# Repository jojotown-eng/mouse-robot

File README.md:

# mouse-robot
マイクロマウスで使用するデータを入れておくリポジトリ

### design
機体のcadデータを入れるファイル

### firmware
マウス内のプログラムデータを入れるフォルダ

### PCB
基板関連のデータを入れる

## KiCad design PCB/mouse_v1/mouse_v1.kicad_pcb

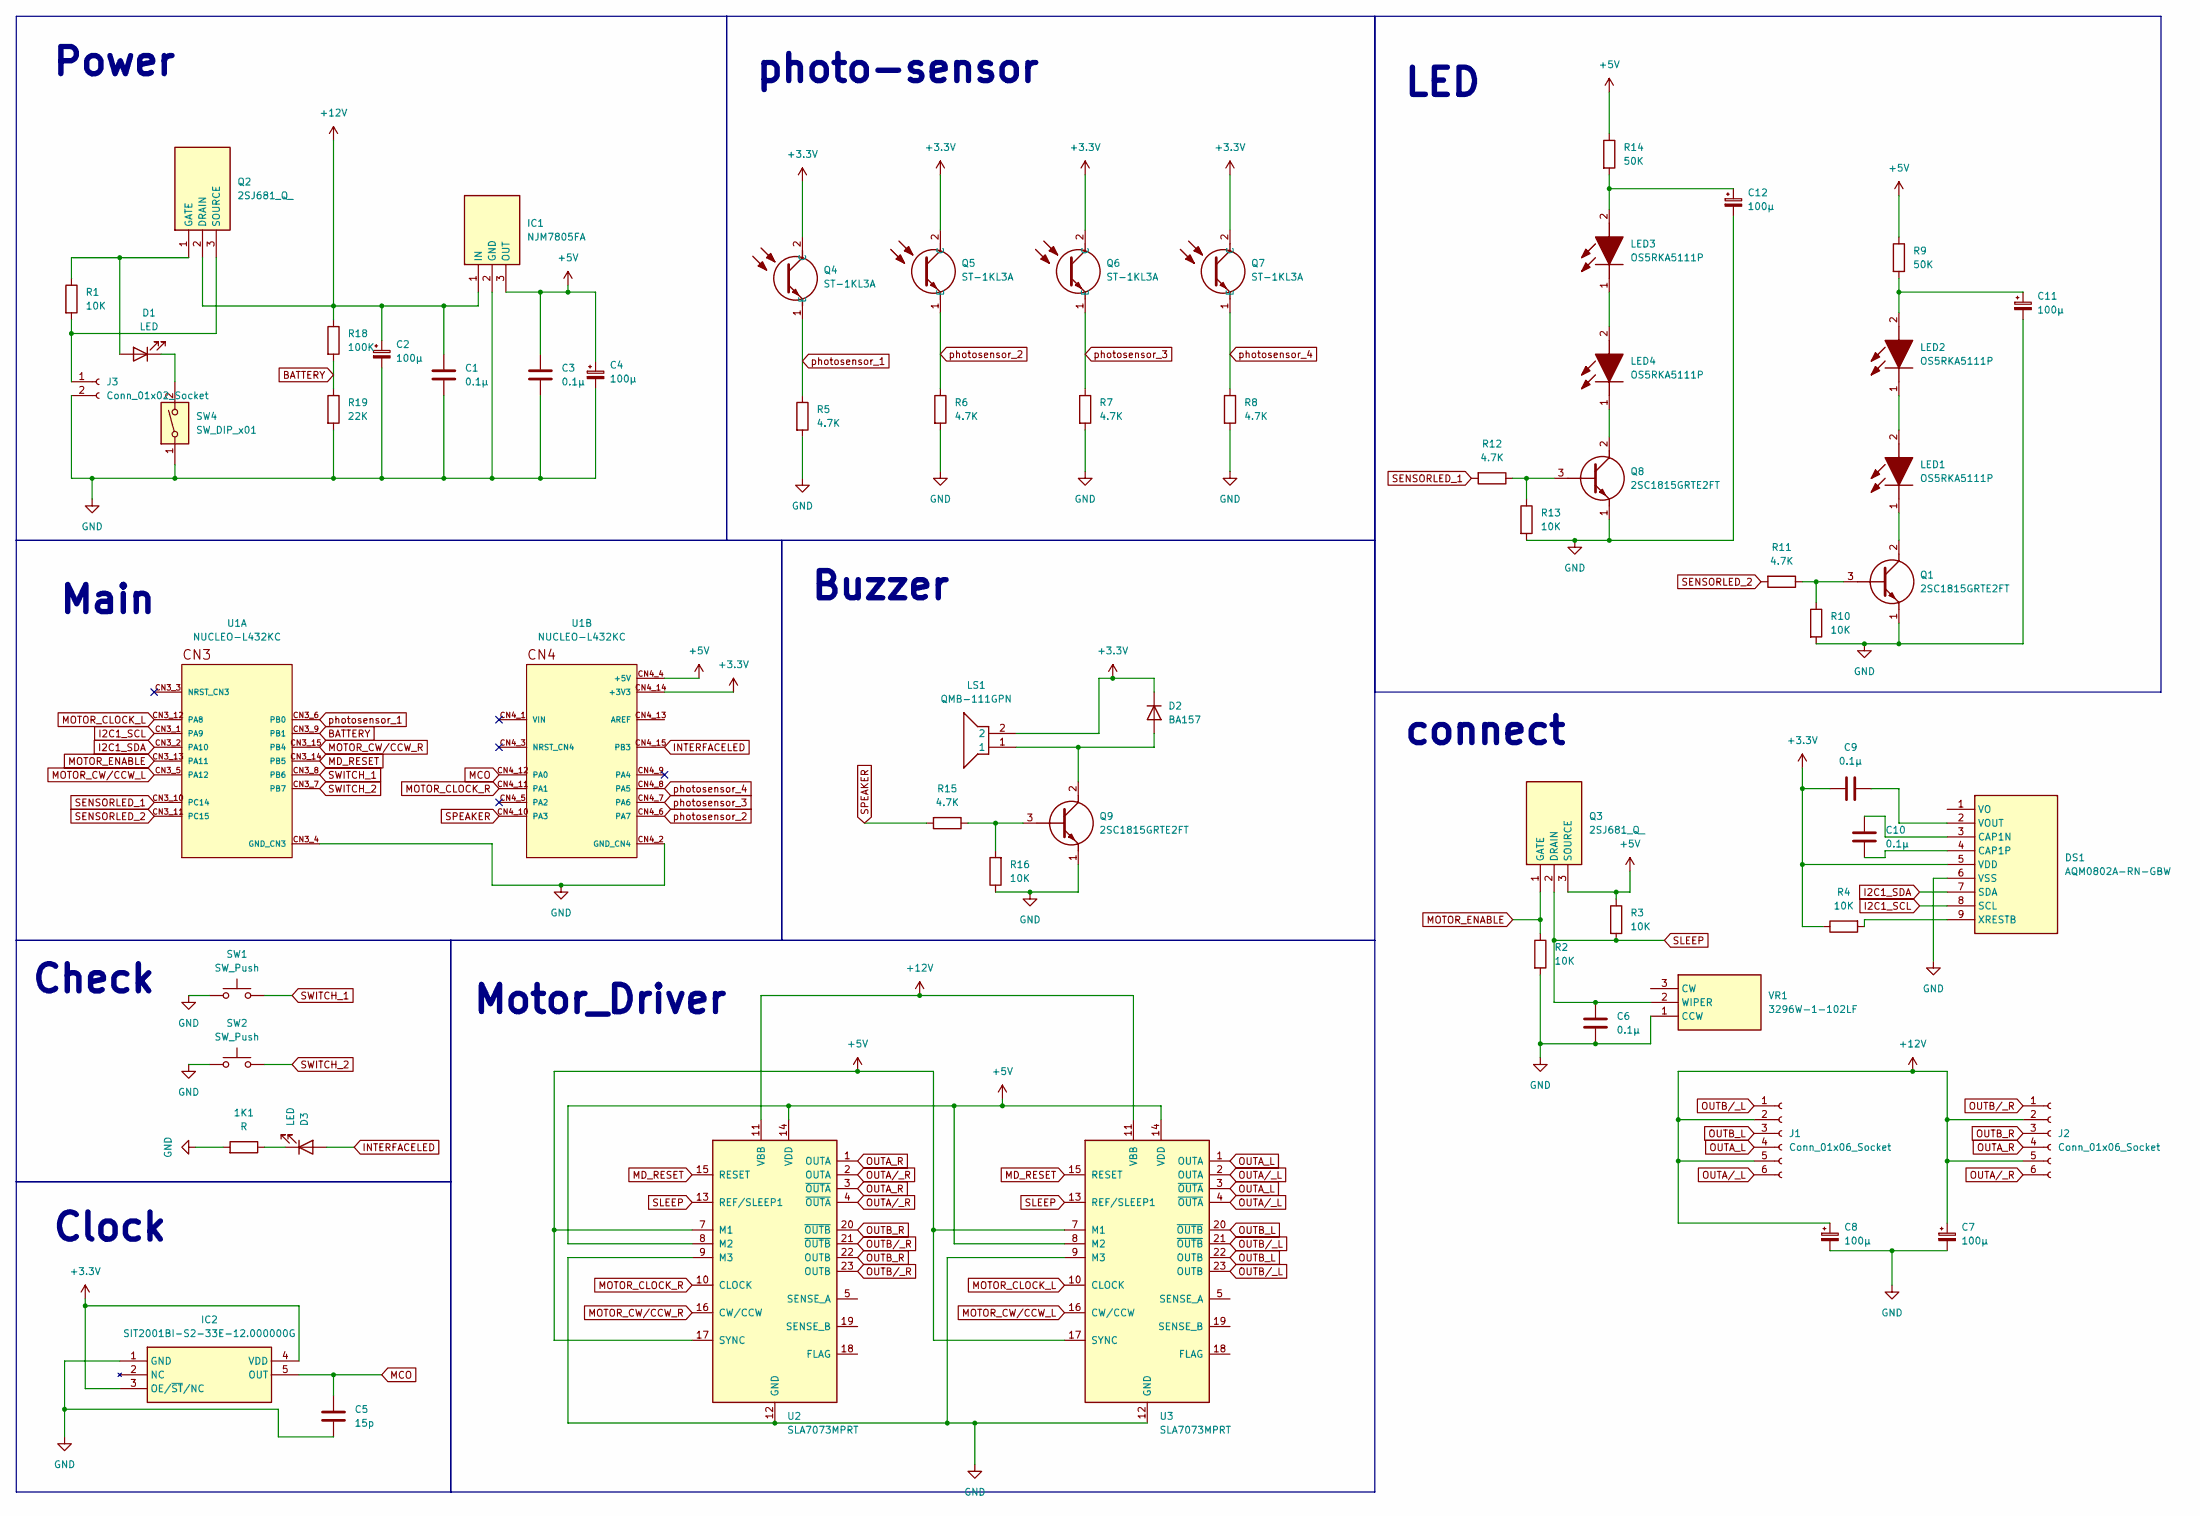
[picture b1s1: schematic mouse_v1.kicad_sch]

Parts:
1K1: R; R_0603_1608Metric_Pad0.98x0.95mm_HandSolder
C1, C3, C6, C9, C10: 0.1μ; C_0603_1608Metric
C2, C4, C7, C8, C11, C12: 100μ; CP_Radial_D6.3mm_P2.50mm
C5: 15p; C_0603_1608Metric
D1, D3: LED; LED_0603_1608Metric
D2: BA157; D_0603_1608Metric
DS1: AQM0802A-RN-GBW; AQM0802ARNGBW; Manufacturer_Part_Number AQM0802A-RN-GBW
IC1: NJM7805FA; TO254P500X1000X2170-3P; Manufacturer_Part_Number NJM7805FA
IC2: SIT2001BI-S2-33E-12.000000G; SOT95P280X130-5N; Manufacturer_Part_Number SIT2001BI-S2-33E-12.000000G
J1, J2: Conn_01x06_Socket; JST_XH_B6B-XH-A_1x06_P2.50mm_Vertical
J3: Conn_01x02_Socket; JST_XH_B2B-XH-A_1x02_P2.50mm_Vertical
LED1, LED2, LED3, LED4: OS5RKA5111P; Manufacturer_Part_Number OS5RKA5111P
LS1: QMB-111GPN; QMB111GPN; Manufacturer_Part_Number QMB-111GPN
Q1, Q8, Q9: 2SC1815GRTE2FT; SOT-23; Manufacturer_Part_Number 2SC1815GRTE2FT
Q2, Q3: 2SJ681_Q_; TO230P250X650X900-3P; Manufacturer_Part_Number 2SJ681(Q)
Q4, Q5, Q6, Q7: ST-1KL3A; ST1KL3A; Manufacturer_Part_Number ST-1KL3A
R1, R2, R3, R4, R10, R13, R16: 10K; R_0603_1608Metric_Pad0.98x0.95mm_HandSolder
R5, R6, R7, R8, R11, R12, R15: 4.7K; R_0603_1608Metric_Pad0.98x0.95mm_HandSolder
R9, R14: 50K; R_0603_1608Metric_Pad0.98x0.95mm_HandSolder
R18: 100K; R_0603_1608Metric_Pad0.98x0.95mm_HandSolder
R19: 22K; R_0603_1608Metric_Pad0.98x0.95mm_HandSolder
SW1, SW2: SW_Push; SW_PUSH_6mm_H7.3mm
SW4: SW_DIP_x01; SW_DIP_SPSTx01_Slide_9.78x4.72mm_W7.62mm_P2.54mm
U1: NUCLEO-L432KC; MODULE_NUCLEO-L432KC; PARTREV N/A
U2, U3: SLA7073MPRT
VR1: 3296W-1-102LF; 3296W1102LF; Manufacturer_Part_Number 3296W-1-102LF

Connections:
+3.3V: C9.1, D2.1 (K), DS1.5 (VDD), IC2.3 (OE/~ST/NC), IC2.4 (VDD), LS1.2, Q4.2 (C), Q5.2 (C), Q6.2 (C), Q7.2 (C), R4.1, U1.CN4_14 (+3V3)
+5V: C3.1, C4.1, IC1.3 (OUT), Q3.3 (SOURCE), R3.1, R9.1, R14.1, U1.CN4_4 (+5V), U2.7 (M1), U2.8 (M2), U2.14 (VDD), U2.17 (SYNC), U3.7 (M1), U3.8 (M2), U3.14 (VDD), U3.17 (SYNC)
+12V: C1.1, C2.1, C7.1, C8.1, IC1.1 (IN), J1.2, J1.5, J2.2, J2.5, Q2.2 (DRAIN), R18.1, U2.11 (VBB), U3.11 (VBB)
BATTERY: R18.2, R19.1, U1.CN3_9 (PB1)
GND: 1K1.2, C1.2, C2.2, C3.2, C4.2, C5.2, C6.2, C7.2, C8.2, C11.2, C12.2, DS1.6 (VSS), IC1.2 (GND), IC2.1 (GND), J3.2, Q1.1 (E), Q8.1 (E), Q9.1 (E), R2.2, R5.2, R6.2, R7.2, R8.2, R10.2, R13.2, R16.1, R19.2, SW1.1, SW2.1, SW4.1, U1.CN3_4 (GND_CN3), U1.CN4_2 (GND_CN4), U2.9 (M3), U2.12 (GND), U3.9 (M3), U3.12 (GND), VR1.1 (CCW)
I2C1_SCL: DS1.8 (SCL), U1.CN3_1 (PA9)
I2C1_SDA: DS1.7 (SDA), U1.CN3_2 (PA10)
INTERFACELED: D3.2 (A), U1.CN4_15 (PB3)
MCO: C5.1, IC2.5 (OUT), U1.CN4_12 (PA0)
MD_RESET: U1.CN3_14 (PB5), U2.15 (RESET), U3.15 (RESET)
MOTOR_CLOCK_L: U1.CN3_12 (PA8), U3.10 (CLOCK)
MOTOR_CLOCK_R: U1.CN4_11 (PA1), U2.10 (CLOCK)
MOTOR_CW/CCW_L: U1.CN3_5 (PA12), U3.16 (CW/CCW)
MOTOR_CW/CCW_R: U1.CN3_15 (PB4), U2.16 (CW/CCW)
MOTOR_ENABLE: Q3.1 (GATE), R2.1, U1.CN3_13 (PA11)
unnamed: D1.2 (A), Q2.1 (GATE), R1.1
unnamed: D1.1 (K), SW4.2
unnamed: D2.2 (A), LS1.1, Q9.2 (C)
unnamed: 1K1.1, D3.1 (K)
unnamed: C10.2, DS1.3 (CAP1N)
unnamed: C10.1, DS1.4 (CAP1P)
unnamed: C9.2, DS1.2 (VOUT)
unnamed: DS1.9 (XRESTB), R4.2
unnamed: J3.1, Q2.3 (SOURCE), R1.2
unnamed: LED1.2 (A), LED2.1 (K)
unnamed: LED1.1 (K), Q1.2 (C)
unnamed: C11.1, LED2.2 (A), R9.2
unnamed: C12.1, LED3.2 (A), R14.2
unnamed: LED3.1 (K), LED4.2 (A)
unnamed: LED4.1 (K), Q8.2 (C)
unnamed: Q1.3 (B), R10.1, R11.1
unnamed: Q8.3 (B), R12.1, R13.1
unnamed: Q9.3 (B), R15.1, R16.2
OUTA_L: J1.4, U3.1 (OUTA), U3.3 (~OUTA)
OUTA_R: J2.4, U2.1 (OUTA), U2.3 (~OUTA)
OUTA/_L: J1.6, U3.2 (OUTA), U3.4 (~OUTA)
OUTA/_R: J2.6, U2.2 (OUTA), U2.4 (~OUTA)
OUTB_L: J1.3, U3.20 (~OUTB), U3.22 (OUTB)
OUTB_R: J2.3, U2.20 (~OUTB), U2.22 (OUTB)
OUTB/_L: J1.1, U3.21 (~OUTB), U3.23 (OUTB)
OUTB/_R: J2.1, U2.21 (~OUTB), U2.23 (OUTB)
SENSORLED_1: R12.2, U1.CN3_10 (PC14)
SENSORLED_2: R11.2, U1.CN3_11 (PC15)
SLEEP: C6.1, Q3.2 (DRAIN), R3.2, U2.13 (REF/SLEEP1), U3.13 (REF/SLEEP1), VR1.2 (WIPER)
SPEAKER: R15.2, U1.CN4_10 (PA3)
SWITCH_1: SW1.2, U1.CN3_8 (PB6)
SWITCH_2: SW2.2, U1.CN3_7 (PB7)
photosensor_1: Q4.1 (E), R5.1, U1.CN3_6 (PB0)
photosensor_2: Q5.1 (E), R6.1, U1.CN4_6 (PA7)
photosensor_3: Q6.1 (E), R7.1, U1.CN4_7 (PA6)
photosensor_4: Q7.1 (E), R8.1, U1.CN4_8 (PA5)

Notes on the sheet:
photo-sensor
Check
Power
connect
Buzzer
Motor_Driver
Main
LED
Clock

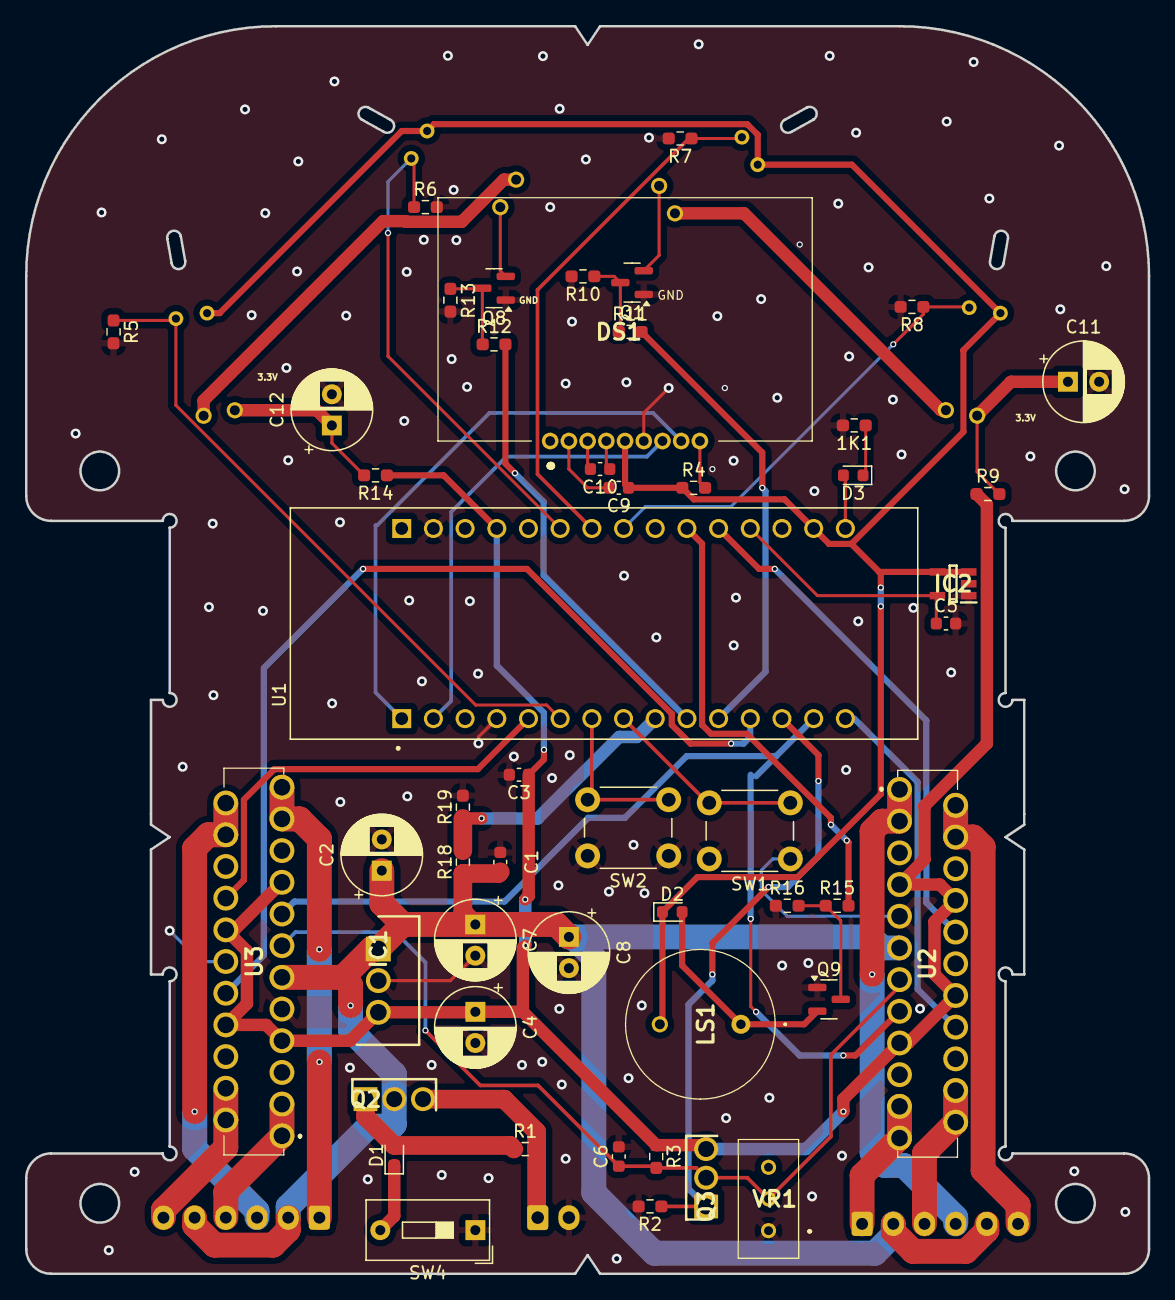
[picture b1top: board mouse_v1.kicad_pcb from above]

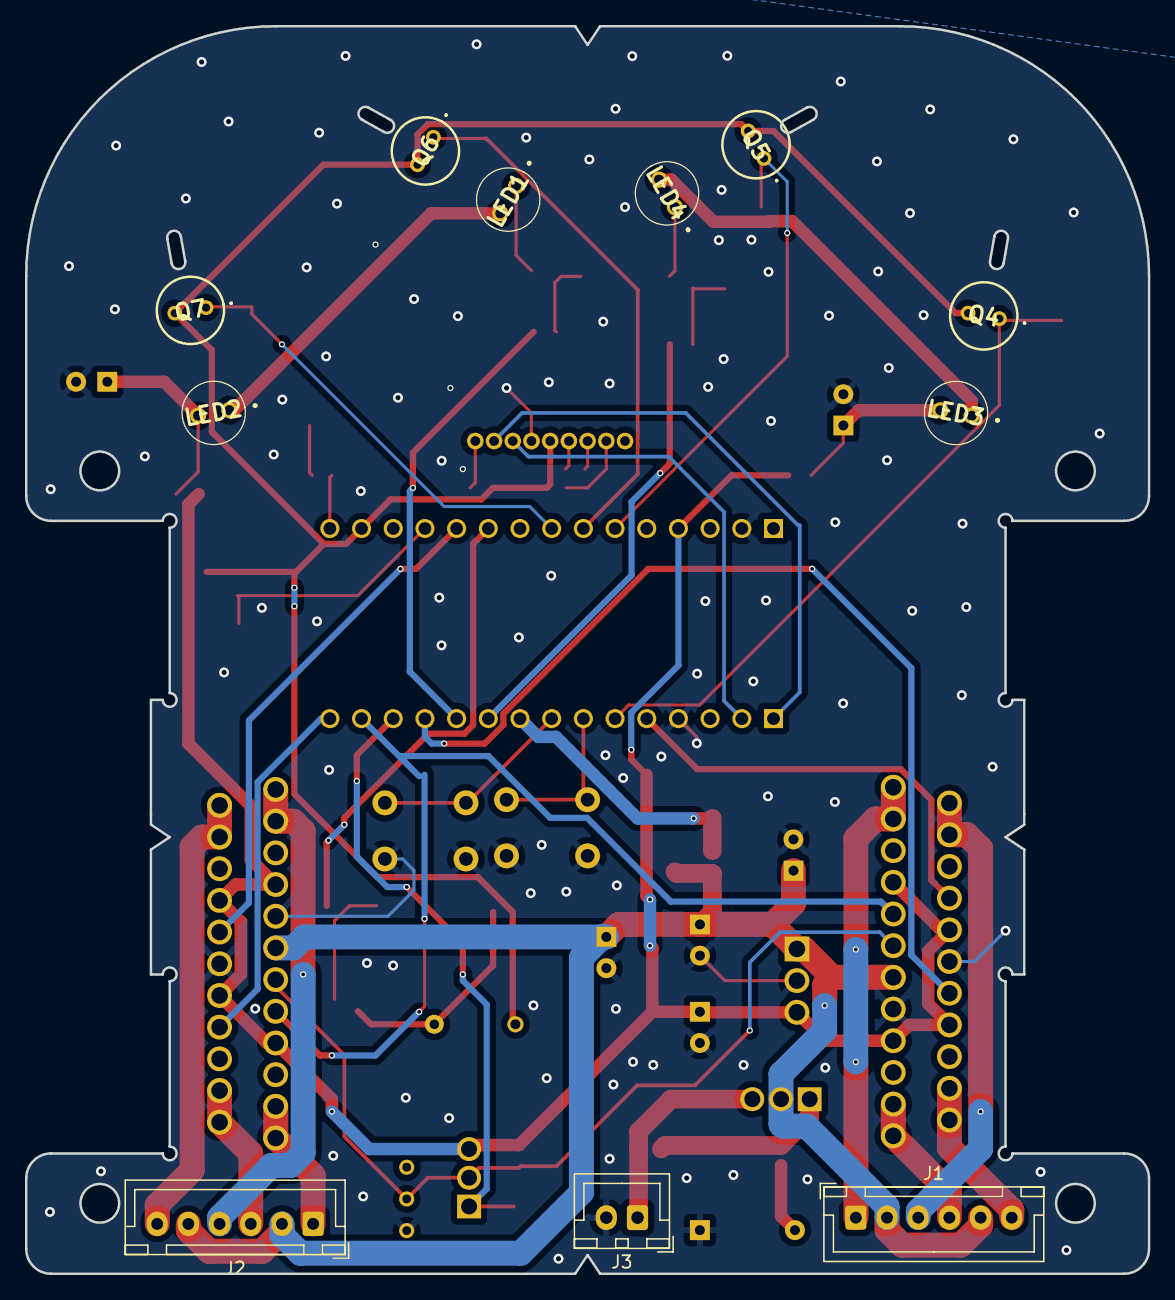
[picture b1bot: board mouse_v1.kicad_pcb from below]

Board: 2 copper layers, 90.0 x 100.0 mm, 61 parts (11 on the bottom side), 51 nets.

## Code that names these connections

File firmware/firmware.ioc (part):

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Mcu.Name=STM32L432K(B-C)Ux
Mcu.Package=UFQFPN32
Mcu.UserName=STM32L432KCUx
PA10.GPIOParameters=GPIO_Label
PA10.GPIO_Label=switch
PA10.Signal=GPIO_Input
PA11.Mode=CAN_Activate
PA11.Signal=CAN1_RX
PA12.Mode=CAN_Activate
PA12.Signal=CAN1_TX
PA13\ (JTMS-SWDIO).Signal=SYS_JTMS-SWDIO
PA14\ (JTCK-SWCLK).Signal=SYS_JTCK-SWCLK
PA2.Mode=Asynchronous
PA2.Signal=USART2_TX
PA3.Mode=Asynchronous
PA3.Signal=USART2_RX
PA8.Mode=fullDuplex
PA8.Signal=SWPMI1_IO
PA9.Signal=GPIO_Output
PB3\ (JTDO-TRACESWO).GPIOParameters=GPIO_Label
PB3\ (JTDO-TRACESWO).GPIO_Label=LED
PB3\ (JTDO-TRACESWO).Signal=GPIO_Output
PC14-OSC32_IN\ (PC14).Mode=LSE-External-Oscillator
PC14-OSC32_IN\ (PC14).Signal=RCC_OSC32_IN
PC15-OSC32_OUT\ (PC15).Mode=LSE-External-Oscillator
PC15-OSC32_OUT\ (PC15).Signal=RCC_OSC32_OUT
RCC.HSE_VALUE=8000000
board=custom

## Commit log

2024-08-22 Kicadの新規ファイル追加
2024-08-22 soramouse参考プログラム
2024-08-22 須田先輩から頂いた資料
2024-08-25 フットプリントライブラリーの追加
2024-08-31 main,motor_driver,connect,clockの回路図作成
2024-09-05 回路図のデータ作成終了,名前振り開始
2024-09-09 回路図の名前振り終了
2024-09-09 capactorを適当にフットプリント振った
2024-09-19 フットプリントを途中まで割り当てて,外部からインポートした部品はできていない
2024-09-20 基板のフットプリント完了
2024-09-20 READMEの編集を行った
2024-09-22 抵抗やコンデンサに具体的な値を明示した
2024-09-23 配線完了,元のデータはsensorLEDのフラグの値が両方1になっていた
2024-09-23 README少し変更した
2024-09-28 アートワークを部品ごとに区分けした
2024-09-28 配線が短くなるように配線した,I2Cは長くなった
2024-09-28 配線完了した(埋め込んだcadがおかしいかも)
2024-09-30 穴の位置に備品があったから少し配置を変えた
2024-10-03 残りのコミット
2024-11-09 配線完了(仮)
2024-11-09 基板完成
2024-11-09 未配線部分を配線した
2024-11-18 再配線完了
2024-11-23 LEDのコンデンサ部分の配線を太くした
2025-02-19 ファイルを開いたせいで起きた変更
2025-02-22 コードを生成した(LEDの実験のため)
2025-02-22 Lチカできた
2025-02-22 Revert "Lチカできた"
    This reverts commit e3f75234c185cfba6b6a0cced84f349a181752c7.
2025-03-01 環境設定をしてビルドまではした。動作しない原因を特定しないと
2025-04-05 スイッチのクラス部分を追加した
